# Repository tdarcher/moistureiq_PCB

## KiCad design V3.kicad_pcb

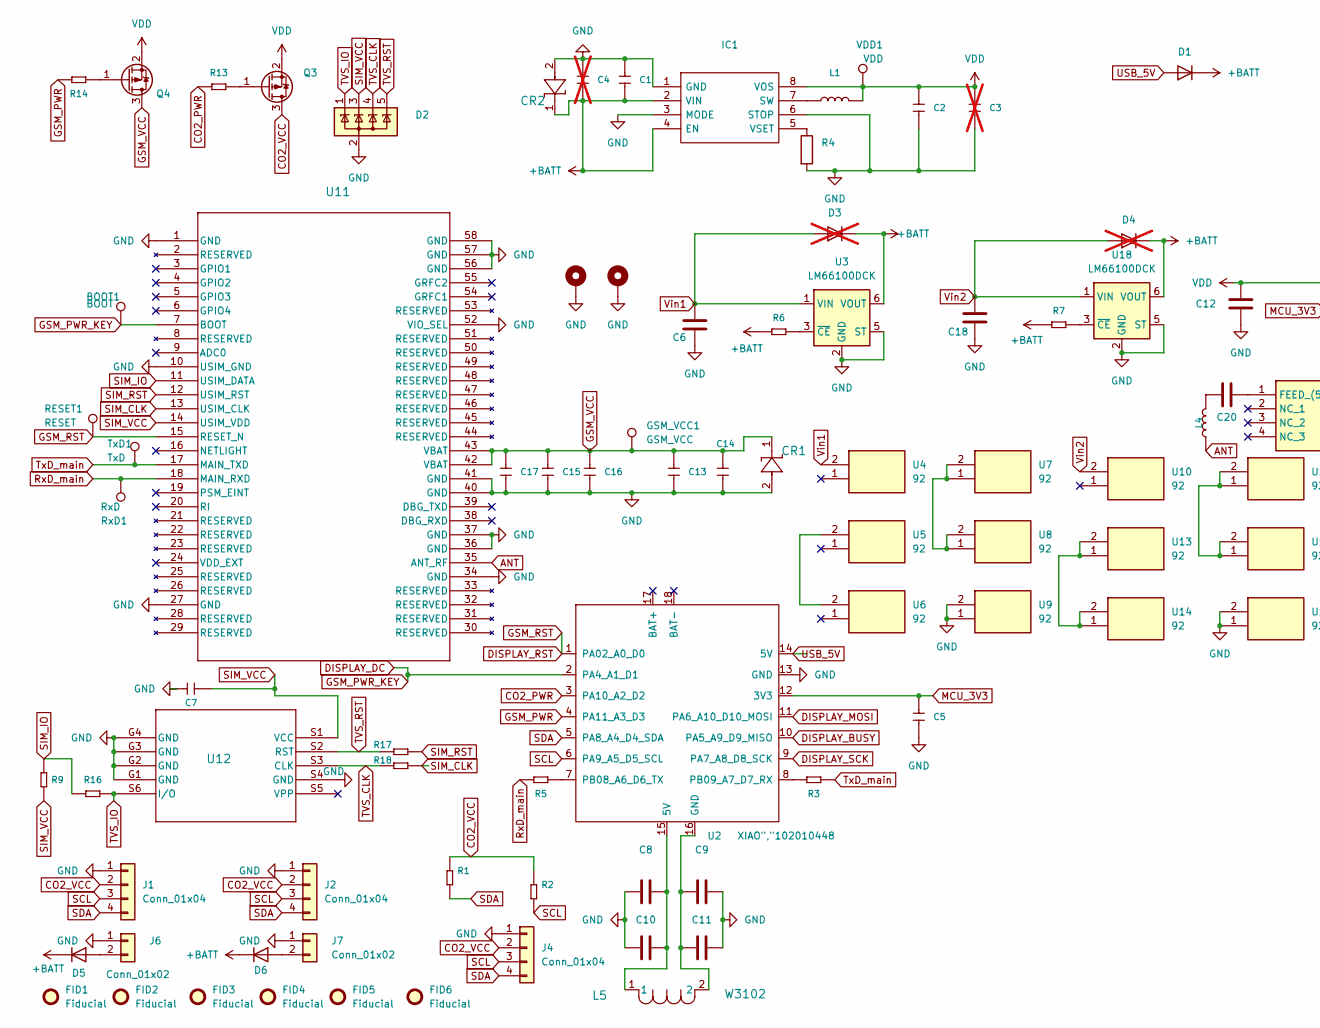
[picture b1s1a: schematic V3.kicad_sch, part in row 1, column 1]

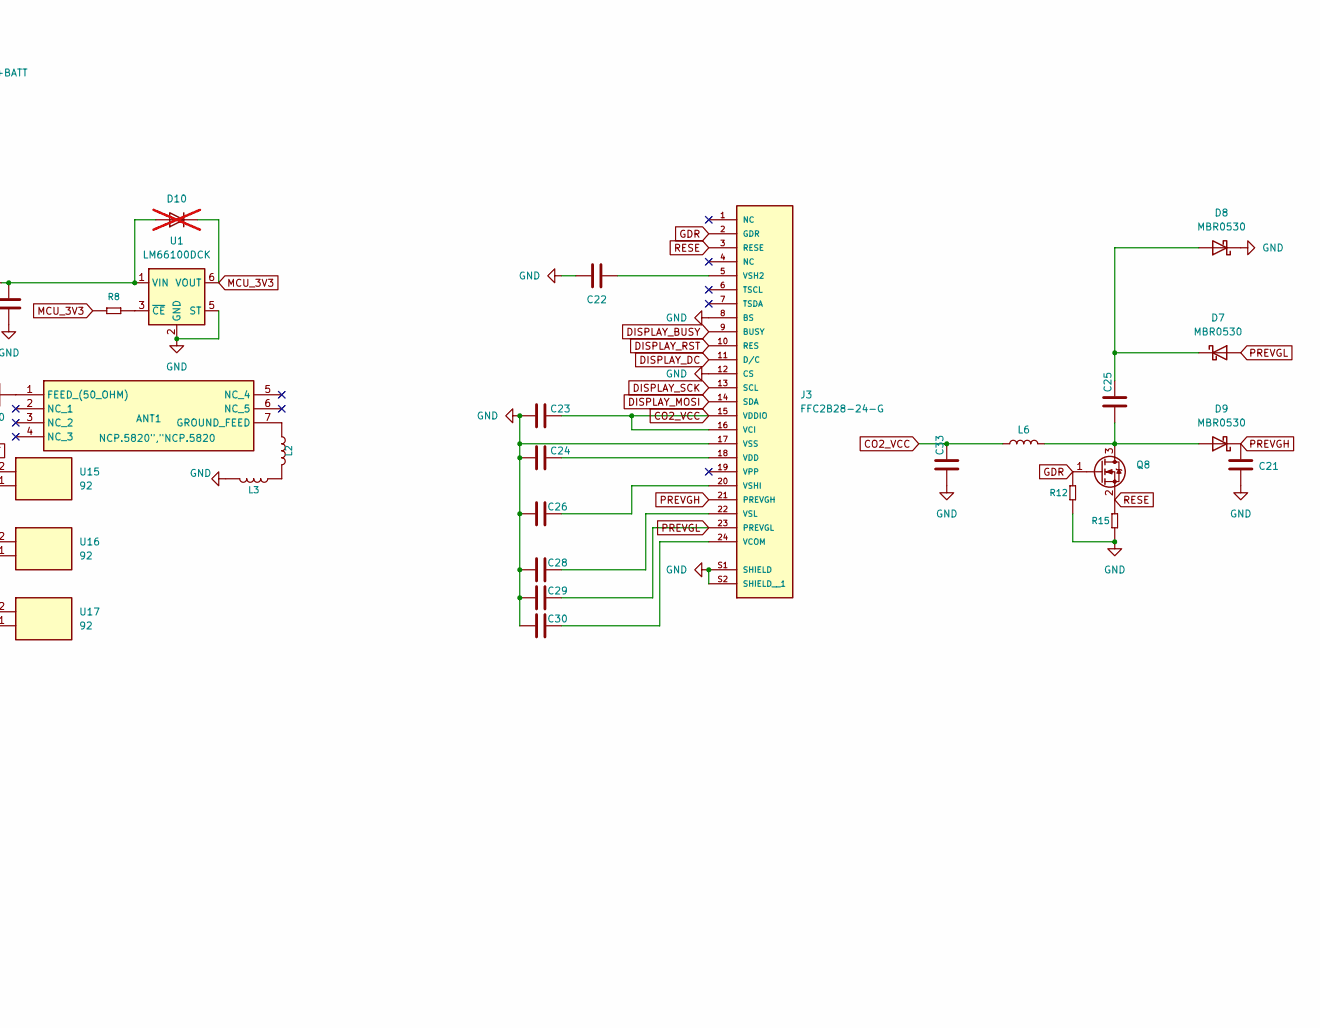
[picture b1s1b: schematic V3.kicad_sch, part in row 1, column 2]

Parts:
ANT1: NCP.5820","NCP.5820; NCP5820; Mouser Part Number 960-NCP5820
BOOT1: BOOT; TestPoint_Pad_1.0x1.0mm
C1, C2, C5: 10uF","EMK212BJ106KG-T; C0805; MPN EMK212BJ106KG-T
C3, C4: 10uF","EMK212BJ106KG-T; C0805; MPN EMK212BJ106KG-T; not fitted
C6, C12, C18, C21, C22, C23, C24, C26, C28, C29, C30: 1uF",CC0603KRX5R7BB105; C0603
C7, C16: 100nF","CC0805KRX7R9BB104; C0805; MPN CC0805KRX7R9BB104
C8: 51pF","06031U510GAT2A; C0603; mpn GCM1885C2A331JA16D
C9: 51pF","06031U510GAT2A; C0603
C10, C11: 3.6pF","CBR06C369B5GAC; C0603
C13, C14: 47uF","MSASL21GBB5476MTNA01; C0805; MPN MSASL21GBB5476MTNA01
C15: 100pF","CC0805JRNPO9BN101; C0805; MPN CC0805JRNPO9BN101
C17: 22pF","0805CG220J500NT; C0805; MPN 0805CG220J500NT
C20: 0.5pF","CBR06C508B5GAC; C0603; mpn CBR06C508B5GAC
C25, C33: 4.7uF","CL10A475KP8NNNC; C0603
CR1, CR2: CUHZ5V6_H3F","CUHZ5V6_H3F; ZDO_30V_H3F_TOS
D1, D5, D6: NSR0520V2","NSR0520V2; D_SOD-523
D2: SP0504BAHTG","SP0504BAHTG; SOT-23-5
D3, D4, D10: NSR0520V2","NSR0520V2; D_SOD-523; not fitted
D7, D8, D9: MBR0530; D_SOD-123
FID1, FID2, FID3, FID4, FID5, FID6: Fiducial; Fiducial_1mm_Mask2mm
GSM_VCC1: GSM_VCC; TestPoint_Pad_1.0x1.0mm
H1, H2: MountingHole_Pad_MP; MountingHole_2.7mm_M2.5_ISO14580_Pad
IC1: TPS62840DLCR","TPS62840DLCR; SON50P150X200X100-8N-D; Mouser Part Number 595-TPS62840DLCR
J1, J2, J4: Conn_01x04; PinSocket_1x04_P2.54mm_Vertical
J3: FFC2B28-24-G; GCT_FFC2B28-24-G; PARTREV A
J6, J7: Conn_01x02; PinHeader_1x02_P2.54mm_Vertical
L1: 2.2uH","DFE201612E-2R2M=P2; L0806; MPN DFE201612E-2R2M=P2
L2: 1.5nH","LRC0603CS1N5GV001T; L_0603_1608Metric; MPN RS-03000JT
L3: 6.8nH","LRC0402CJ6N8GV001T; L_0603_1608Metric; MPN RS-03000JT
L4: 33nH","LRC0603CJ33NGV001T; L_0603_1608Metric; MPN RS-03000JT
L5: W3102; IND_3102_PUL
L6: 10uH","LSXND4040TKL100MDG; IND_LSXN&slash_LSXP_4040TK_TAY
Q3, Q4: FDN304P","FDN304P; SOT-23
Q8: SI1308EDL","SI1308EDL; MOSFET_8EDL-T1-GE3_VIS
R1, R2, R6, R7, R8, R9, R12: 10K","RC0603JR-0710KL; R0603; MPN RC0603JR-0710KL
R3: 100R","301010090; R0603; MPN 301010090
R4: 267K","RK73H1JTTD2673F; R0603; MPN AC0805FR-07267KL
R5, R13, R14: 100R","301010090; R0603; MPN ESR03EZPF1000
R15: 3R","3R; R0603; MPN RC0603JR-0710KL
R16, R17, R18: 22R","22R; R0603; MPN ESR03EZPF1000
RESET1: RESET; TestPoint_Pad_1.0x1.0mm
RxD1: RxD; TestPoint_Pad_1.0x1.0mm
TxD1: TxD; TestPoint_Pad_1.0x1.0mm
U1, U3, U18: LM66100DCK; SOT-363_SC-70-6
U2: XIAO","102010448; MOUDLE16P-SMD-2.54-21X17.8MM
U4, U5, U6, U7, U8, U9, U10, U13, U14, U15, U16, U17: 92; Mouser Part Number 534-092
U11: BC660KGLAA-I03-SNASA","BC660KGLAA-I03-SNASA; BC66_QWS
U12: 1042240820","1042240820; 1042240820_MOL
VDD1: VDD; TestPoint_Pad_1.0x1.0mm

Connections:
+BATT: C1.2, C4.2, CR2.1, D1.1 (K), D3.1 (K), D4.1 (K), D5.1 (K), D6.1 (K), IC1.2 (VIN), IC1.4 (EN), R6.1, R7.1, U3.6 (VOUT), U18.6 (VOUT)
ANT: L4.1, U11.35 (ANT_RF)
CO2_PWR: R13.2, U2.3 (PA10_A2_D2)
CO2_VCC: C23.1, C33.1, J1.2, J2.2, J3.15 (VDDIO), J3.16 (VCI), J4.2, L6.1, Q3.3 (D), R1.2, R2.2
DISPLAY_BUSY: J3.9 (BUSY), U2.10 (PA5_A9_D9_MISO)
DISPLAY_DC: BOOT1.1, J3.11 (D/C), U2.2 (PA4_A1_D1), U11.7 (BOOT)
DISPLAY_MOSI: J3.14 (SDA), U2.11 (PA6_A10_D10_MOSI)
DISPLAY_RST: J3.10 (RES), RESET1.1, U2.1 (PA02_A0_D0), U11.15 (RESET_N)
DISPLAY_SCK: J3.13 (SCL), U2.9 (PA7_A8_D8_SCK)
GDR: J3.2 (GDR), Q8.1 (G), R12.2
GND: C1.1, C2.2, C3.2, C4.1, C5.2, C6.1, C7.2, C8.2, C9.2, C10.2, C11.2, C12.2, C13.2, C14.2, C15.2, C16.2, C17.2, C18.1, C21.2, C22.2, C23.2, C24.2, C26.2, C28.2, C29.2, C30.2, C33.2, CR1.2, CR2.2, D2.2 (A), D8.1 (K), H1.1, H2.1, IC1.1 (GND), IC1.3 (MODE), IC1.6 (STOP), J1.1, J2.1, J3.8 (BS), J3.12 (CS), J3.17 (VSS), J3.S1 (SHIELD), J3.S2 (SHIELD__1), J4.1, J6.1, J7.1, L3.2, R4.2, R12.1, R15.1, U1.2 (GND), U1.5 (ST), U2.13 (GND), U3.2 (GND), U3.5 (ST), U9.1, U9.2, U11.1 (GND), U11.10 (USIM_GND), U11.27 (GND), U11.34 (GND), U11.36 (GND), U11.37 (GND), U11.40 (GND), U11.41 (GND), U11.52 (VIO_SEL), U11.56 (GND), U11.57 (GND), U11.58 (GND), U12.G1 (GND), U12.G2 (GND), U12.G3 (GND), U12.G4 (GND), U12.S4 (GND), U17.1, U17.2, U18.2 (GND), U18.5 (ST)
GSM_PWR: R14.1, U2.4 (PA11_A3_D3)
GSM_VCC: C13.1, C14.1, C15.1, C16.1, C17.1, CR1.1, GSM_VCC1.1, Q4.3 (D), U11.42 (VBAT), U11.43 (VBAT)
MCU_3V3: C5.1, D10.1 (K), R8.1, U1.6 (VOUT), U2.12 (3V3)
unnamed: ANT1.1 (FEED_(50_OHM)), C20.1
unnamed: ANT1.7 (GROUND_FEED), L2.1
unnamed: C8.1, C10.1, L5.1, U2.15 (5V)
unnamed: C9.1, C11.1, L5.2, U2.16 (GND)
unnamed: C20.2, L4.2
unnamed: D5.2 (A), J6.2
unnamed: D6.2 (A), J7.2
unnamed: C25.1, D7.1 (K), D8.2 (A)
unnamed: C25.2, D9.2 (A), L6.2, Q8.3 (D)
unnamed: IC1.7 (SW), L1.1
unnamed: IC1.5 (VSET), R4.1
unnamed: C30.1, J3.24 (VCOM)
unnamed: C24.1, J3.18 (VDD)
unnamed: C22.1, J3.5 (VSH2)
unnamed: C26.1, J3.20 (VSHI)
unnamed: C28.1, J3.22 (VSL)
unnamed: L2.2, L3.1
unnamed: Q3.1 (G), R13.1
unnamed: Q4.1 (G), R14.2
unnamed: R8.2, U1.3 (~CE)
unnamed: R5.1, U2.7 (PB08_A6_D6_TX)
unnamed: R3.2, U2.8 (PB09_A7_D7_RX)
unnamed: R6.2, U3.3 (~CE)
unnamed: U5.2, U6.2
unnamed: U7.1, U7.2, U8.1, U8.2
unnamed: U13.1, U13.2, U14.1, U14.2
unnamed: U15.1, U15.2, U16.1, U16.2
unnamed: R7.2, U18.3 (~CE)
PREVGH: C21.1, D9.1 (K), J3.21 (PREVGH)
PREVGL: C29.1, D7.2 (A), J3.23 (PREVGL)
RESE: J3.3 (RESE), Q8.2 (S), R15.2
RxD_main: R5.2, RxD1.1, U11.18 (MAIN_RXD)
SCL: J1.3, J2.3, J4.3, R2.1, U2.6 (PA9_A5_D5_SCL)
SDA: J1.4, J2.4, J4.4, R1.1, U2.5 (PA8_A4_D4_SDA)
SIM_CLK: R18.1, U11.13 (USIM_CLK)
SIM_IO: R9.2, R16.2, U11.11 (USIM_DATA)
SIM_RST: R17.1, U11.12 (USIM_RST)
SIM_VCC: C7.1, D2.3 (K), R9.1, U11.14 (USIM_VDD), U12.S1 (VCC)
TVS_CLK: D2.4 (K), R18.2, U12.S3 (CLK)
TVS_IO: D2.1 (K), R16.1, U12.S6 (I/O)
TVS_RST: D2.5 (K), R17.2, U12.S2 (RST)
TxD_main: R3.1, TxD1.1, U11.17 (MAIN_TXD)
USB_5V: D1.2 (A), U2.14 (5V)
VDD: C2.1, C3.1, C12.1, D10.2 (A), IC1.8 (VOS), L1.2, Q3.2 (S), Q4.2 (S), U1.1 (VIN), VDD1.1
Vin1: C6.2, D3.2 (A), U3.1 (VIN), U4.2
Vin2: C18.2, D4.2 (A), U10.2, U18.1 (VIN)

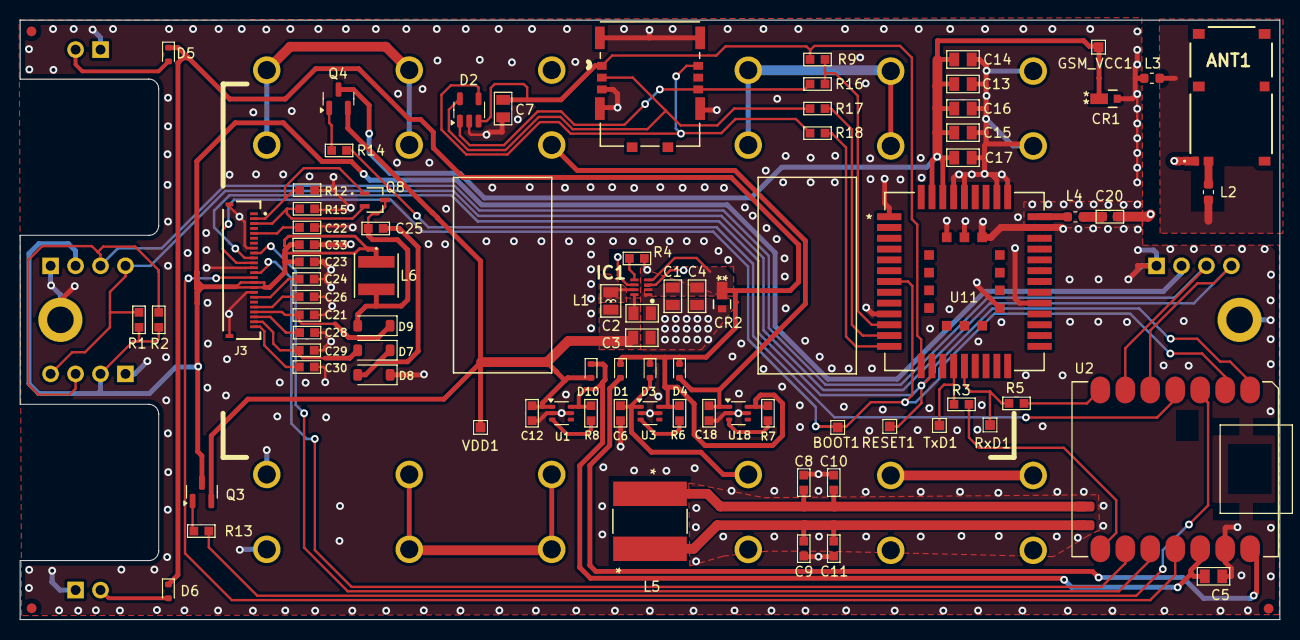
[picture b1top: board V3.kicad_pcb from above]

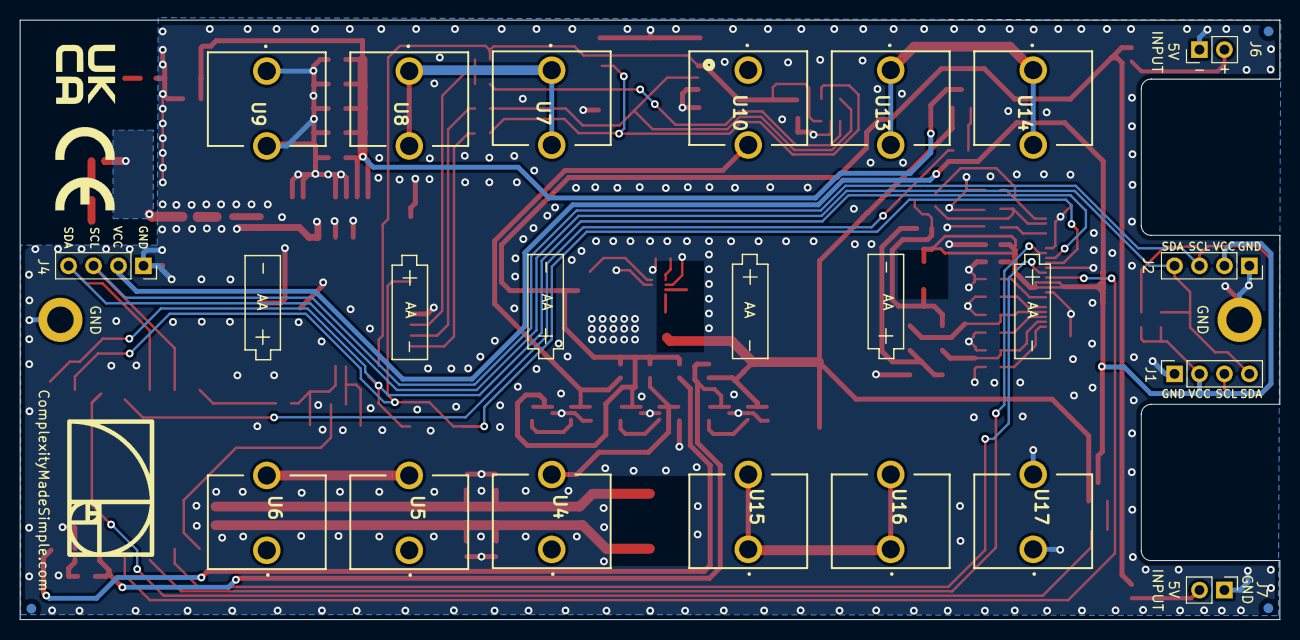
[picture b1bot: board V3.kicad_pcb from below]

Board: 2 copper layers, 128.2 x 61.0 mm, 106 parts (21 on the bottom side), 60 nets.

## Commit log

2024-10-14 build sent to JLCPCB
2024-10-22 add resisors to sim card, move TVS diode, add 3rd i2c header
2024-10-23 add resistors for sim card. Move componets from sticky pads, make extra room for sim card holder
2024-10-23 create production files
2024-10-23 ordred 23/10/2024
2024-10-24 change OR ring to diodes
2024-10-24 replace reverse polarity mosfets with diodes
2024-10-25 revision to review with ideal diode oring
2024-10-25 pre order review
2024-10-25 clean up silk screen
2024-10-25 edit fotprint of xiao module
2024-10-26 order submitted
2024-10-26 regnerate gerber files
